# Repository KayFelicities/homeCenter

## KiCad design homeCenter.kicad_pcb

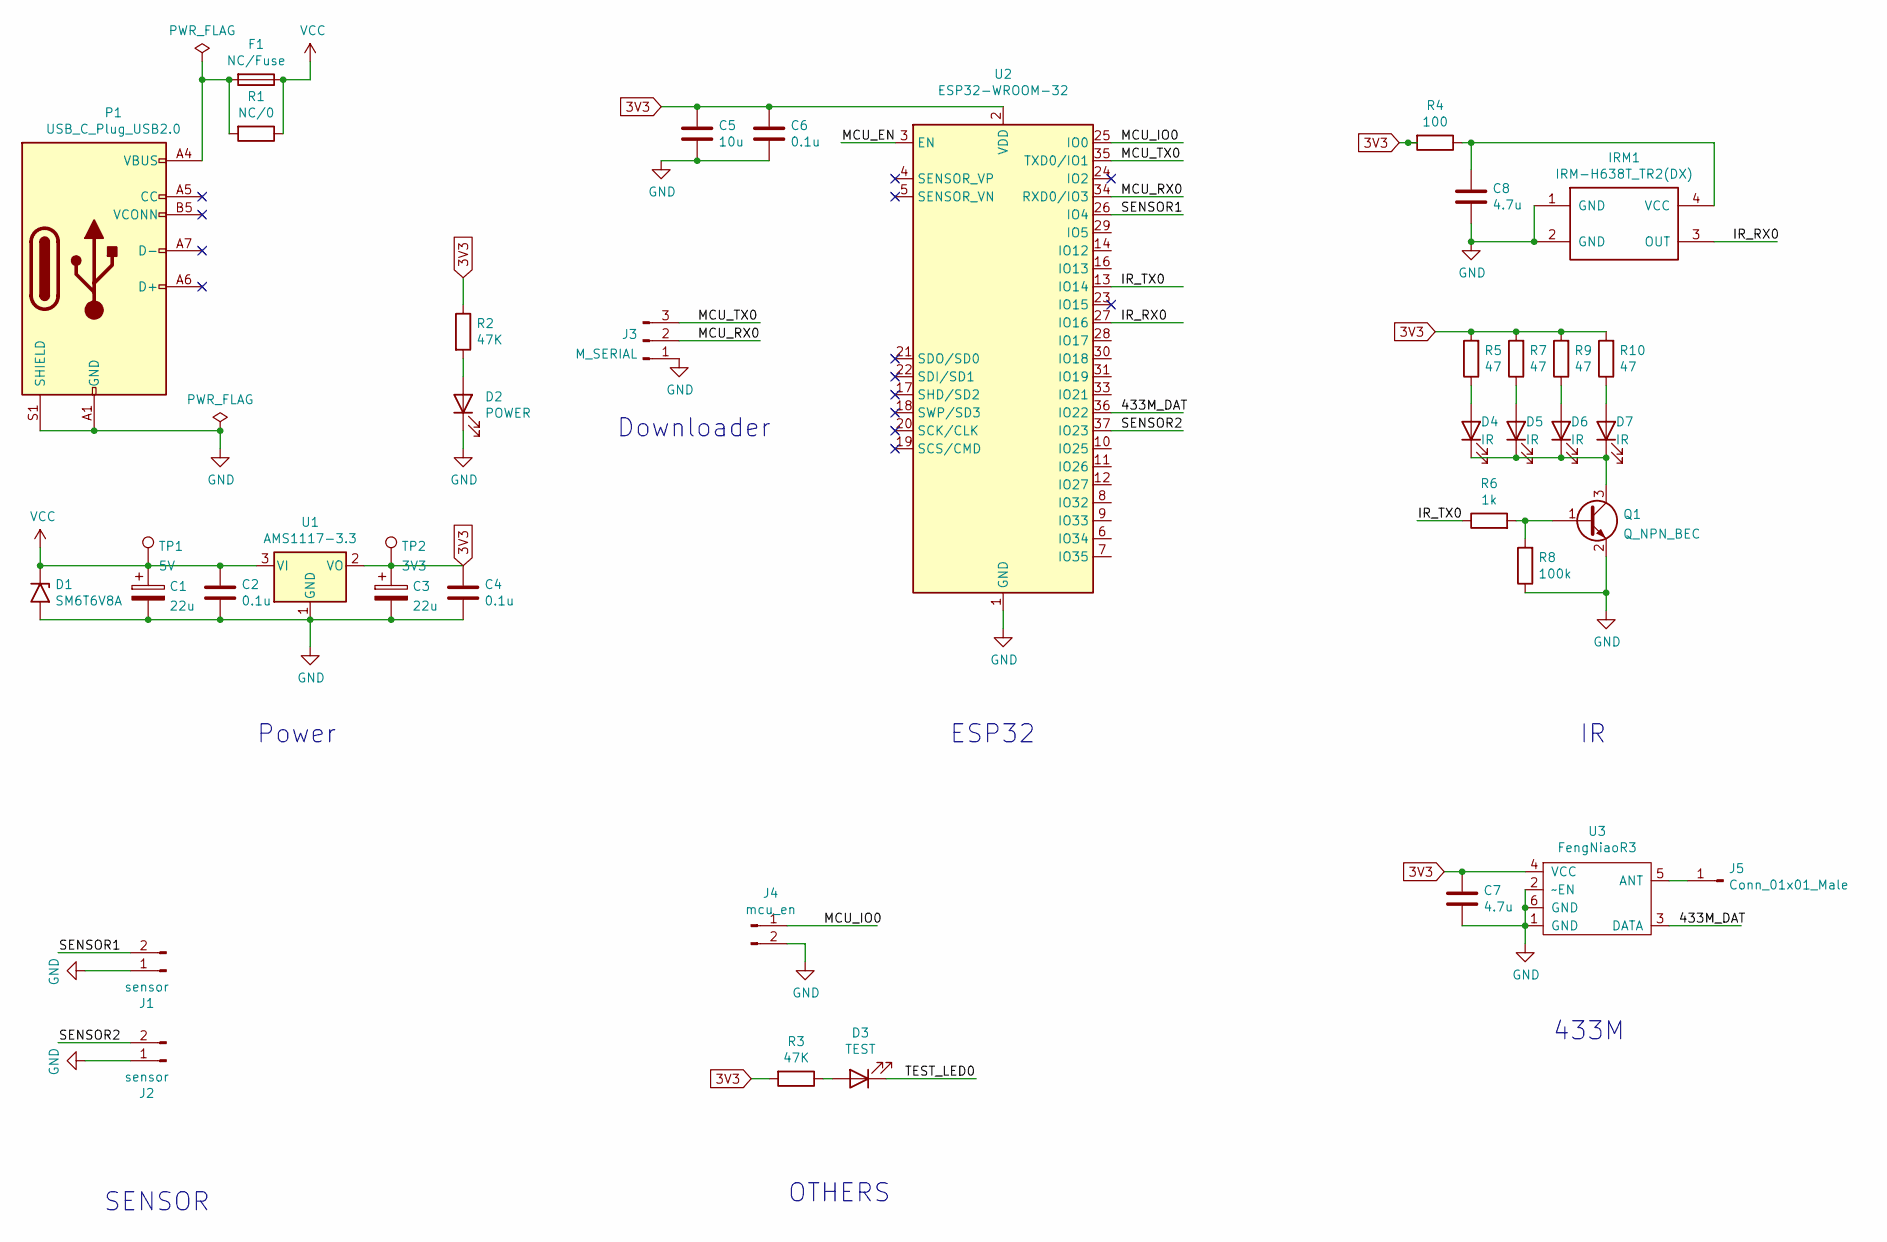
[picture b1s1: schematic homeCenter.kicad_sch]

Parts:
C1, C3: 22u; CAP-SMD_L3.2-W1.6-RD
C2, C4, C6: 0.1u; C_0603_1608Metric
C5: 10u; C_0603_1608Metric
C7, C8: 4.7u; C_0603_1608Metric
D1: SM6T6V8A; D_SOD-523
D2: POWER; LED_0603_1608Metric
D3: TEST; LED_0603_1608Metric
D4, D5, D6, D7: IR; LED-SMD_L3.0-W2.7-RD
F1: NC/Fuse; Fuse_1210_3225Metric
IRM1: IRM-H638T_TR2(DX); SMD_IRM-H638T-TR2-DX
J1, J2: sensor; SH1.0MM-SMD
J3: M_SERIAL; PinHeader_1x03_P2.54mm_Vertical
J4: mcu_en; C_0504_1310Metric_Pad0.83x1.28mm_HandSolder
J5: Conn_01x01_Male; 433M_ANT
P1: USB_C_Plug_USB2.0; USB_C_Receptacle_HRO_TYPE-C-31-M-12
Q1: Q_NPN_BEC; SOT-23
R1: NC/0; R_0603_1608Metric
R2, R3: 47K; R_0603_1608Metric
R4: 100; R_0603_1608Metric
R5, R7, R9, R10: 47; R_0603_1608Metric
R6: 1k; R_0603_1608Metric
R8: 100k; R_0603_1608Metric
TP1: 5V; TestPoint_Pad_D1.0mm
TP2: 3V3; TestPoint_Pad_D1.0mm
U1: AMS1117-3.3; SOT-223-3_TabPin2
U2: ESP32-WROOM-32
U3: FengNiaoR3

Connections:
3V3: C3.1, C4.1, C5.1, C6.1, C7.1, R2.1, R3.2, R4.2, R5.2, R7.2, R9.2, R10.2, TP2.1, U1.2 (VO), U2.2 (VDD), U3.4 (VCC); also elsewhere on the board
/433M_DAT: U2.36 (IO22), U3.3 (DATA)
/IR_RX0: IRM1.3 (OUT), U2.27 (IO16)
/IR_TX0: R6.1, U2.13 (IO14)
/MCU_EN: U2.3 (EN)
/MCU_IO0: J4.1, U2.25 (IO0)
/MCU_RX0: J3.2, U2.34 (RXD0/IO3)
/MCU_TX0: J3.3, U2.35 (TXD0/IO1)
/SENSOR1: J1.2, U2.26 (IO4)
/SENSOR2: J2.2, U2.37 (IO23)
/TEST_LED0: D3.1 (K)
GND: C1.2, C2.2, C3.2, C4.2, C5.2, C6.2, C7.2, C8.2, D1.2 (A2), D2.1 (K), IRM1.1 (GND), IRM1.2 (GND), J1.1, J2.1, J3.1, J4.2, P1.A1 (GND), P1.A12 (GND), P1.B1 (GND), P1.B12 (GND), P1.S1 (SHIELD), Q1.2 (E), R8.1, U1.1 (GND), U2.1 (GND), U2.15 (GND), U2.38 (GND), U2.39 (GND), U3.1 (GND), U3.2 (~EN), U3.6 (GND)
unnamed: C8.1, IRM1.4 (VCC), R4.1
unnamed: D2.2 (A), R2.2
unnamed: D3.2 (A), R3.1
unnamed: D4.1 (K), D5.1 (K), D6.1 (K), D7.1 (K), Q1.3 (C)
unnamed: D4.2 (A), R5.1
unnamed: D5.2 (A), R7.1
unnamed: D6.2 (A), R9.1
unnamed: D7.2 (A), R10.1
unnamed: F1.2, P1.A4 (VBUS), P1.A9 (VBUS), P1.B4 (VBUS), P1.B9 (VBUS), R1.2
unnamed: J5.1, U3.5 (ANT)
unnamed: Q1.1 (B), R6.2, R8.2
VCC: C1.1, C2.1, D1.1 (A1), F1.1, R1.1, TP1.1, U1.3 (VI); also elsewhere on the board

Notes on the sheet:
SENSOR
Power
Downloader
OTHERS
ESP32
433M

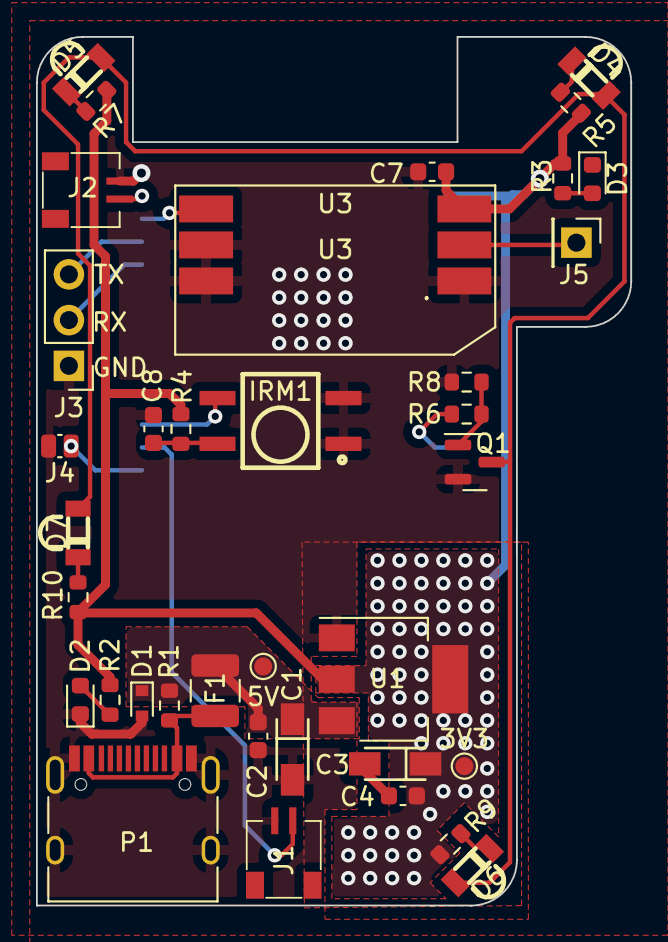
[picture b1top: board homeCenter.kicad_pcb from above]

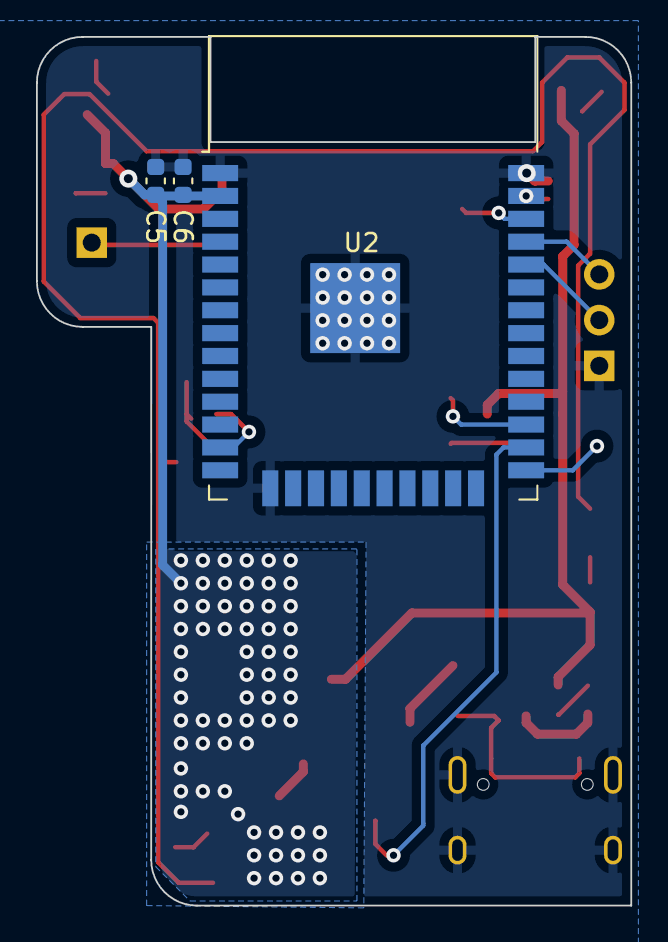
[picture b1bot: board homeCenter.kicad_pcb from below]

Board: 2 copper layers, 33.0 x 48.3 mm, 39 parts (3 on the bottom side), 22 nets.

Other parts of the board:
3V3: 3V3; TestPoint_Pad_D1.0mm
5V: 5V; TestPoint_Pad_D1.0mm

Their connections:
3V3: 3V3.1; also elsewhere on the board
VCC: 5V.1; also elsewhere on the board

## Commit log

2021-06-21 basic
2021-07-02 convert to kicad 4.99
2021-07-03 v0.2
